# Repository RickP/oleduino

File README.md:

OLEDuino
--------

A cheap electronic name badge that can be programmed with the arduino ide. 
The ATMEGA 328 has to be preloaded with the Arduino Pro 8Mhz 3.3V bootloader.
Also chose that board when programming the badge with a 3.3V FTDI board.

All the analog ports are available for addons. 

* A source for the OLED: Search eBay for "128X64 OLED module" and pick the cheapest one with the 7 pin header on top
* A source for a battery: Any small 3.7V lithium polymer battery will do (like the ones for small RC helicopters)
* A source for the charger: http://www.ebay.com/itm/260581913847

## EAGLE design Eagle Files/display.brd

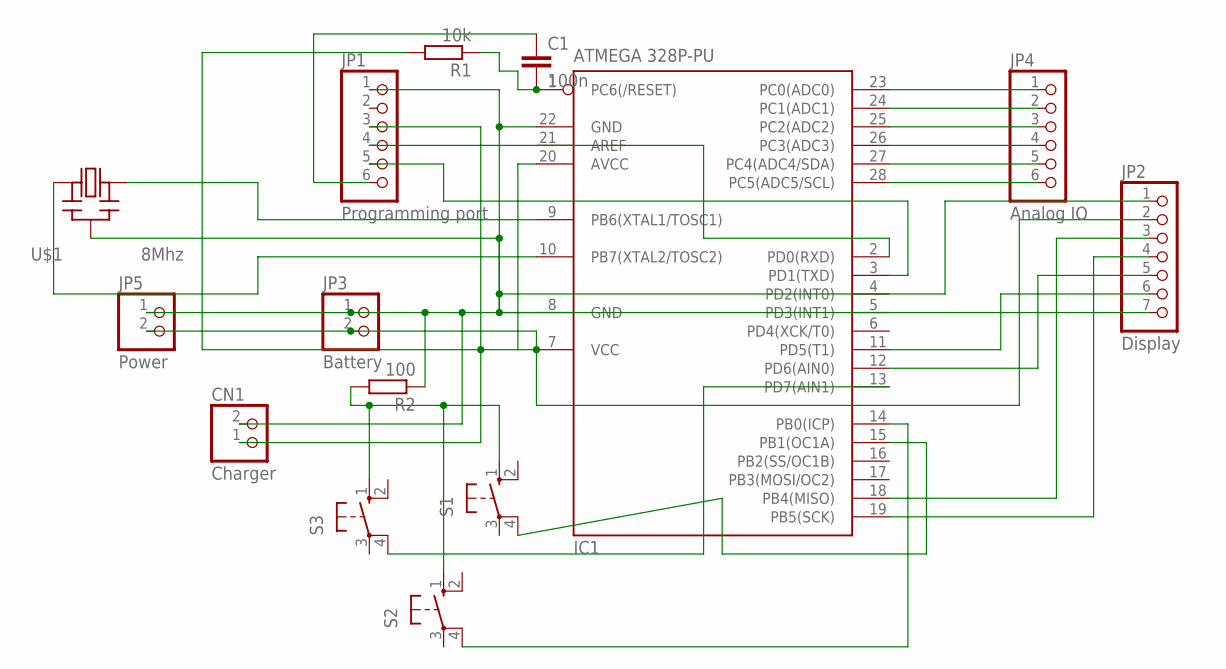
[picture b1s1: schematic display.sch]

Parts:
C1: 100n; C050-025X075
CN1: Charger; JST-PH-2-THM-RA
IC1: ATMEGA 328P-PU; DIL28-3
JP1: Programming port; 1X06/90
JP2: Display; 1X07
JP3: Battery; 1X02
JP4: Analog IO; 1X06-CLEAN
JP5: Power; 1X02
R1: 10k; 0204/7
R2: 100; 0204/7
S1, S3: 10-XX; B3F-10XX
S2: 10-XX; B3F-10XX; MPN B3F-1000
U$1: 8Mhz; CERM_OSC

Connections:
unnamed: IC1.23 (PC0(ADC0)), JP4.1
unnamed: IC1.10 (PB7(XTAL2/TOSC2)), U$1.P$1 (IN)
unnamed: IC1.19 (PB5(SCK)), JP2.4
unnamed: C1.2, IC1.1 (PC6(/RESET)), R1.1
unnamed: IC1.2 (PD0(RXD)), JP1.4
unnamed: IC1.3 (PD1(TXD)), JP1.5
unnamed: IC1.18 (PB4(MISO)), JP2.3
unnamed: CN1.1 (2), IC1.7 (VCC), IC1.20 (AVCC), JP1.3, JP2.2, JP3.2, JP5.2, R1.2
unnamed: IC1.15 (PB1(OC1A)), S1.4 (P1)
unnamed: IC1.13 (PD7(AIN1)), S3.4 (P1)
unnamed: C1.1, JP1.6
unnamed: R2.2, S1.1 (S), S2.1 (S), S3.1 (S)
unnamed: IC1.12 (PD6(AIN0)), JP2.5
unnamed: IC1.9 (PB6(XTAL1/TOSC1)), U$1.P$3 (OUT)
unnamed: IC1.11 (PD5(T1)), JP2.6
unnamed: IC1.14 (PB0(ICP)), S2.4 (P1)
unnamed: IC1.28 (PC5(ADC5/SCL)), JP4.6
unnamed: IC1.27 (PC4(ADC4/SDA)), JP4.5
unnamed: IC1.26 (PC3(ADC3)), JP4.4
unnamed: IC1.25 (PC2(ADC2)), JP4.3
unnamed: IC1.24 (PC1(ADC1)), JP4.2
unnamed: CN1.2 (1), IC1.8 (GND), IC1.22 (GND), JP1.1, JP2.1, JP2.7, JP3.1, JP5.1, R2.1, U$1.P$2 (GND)

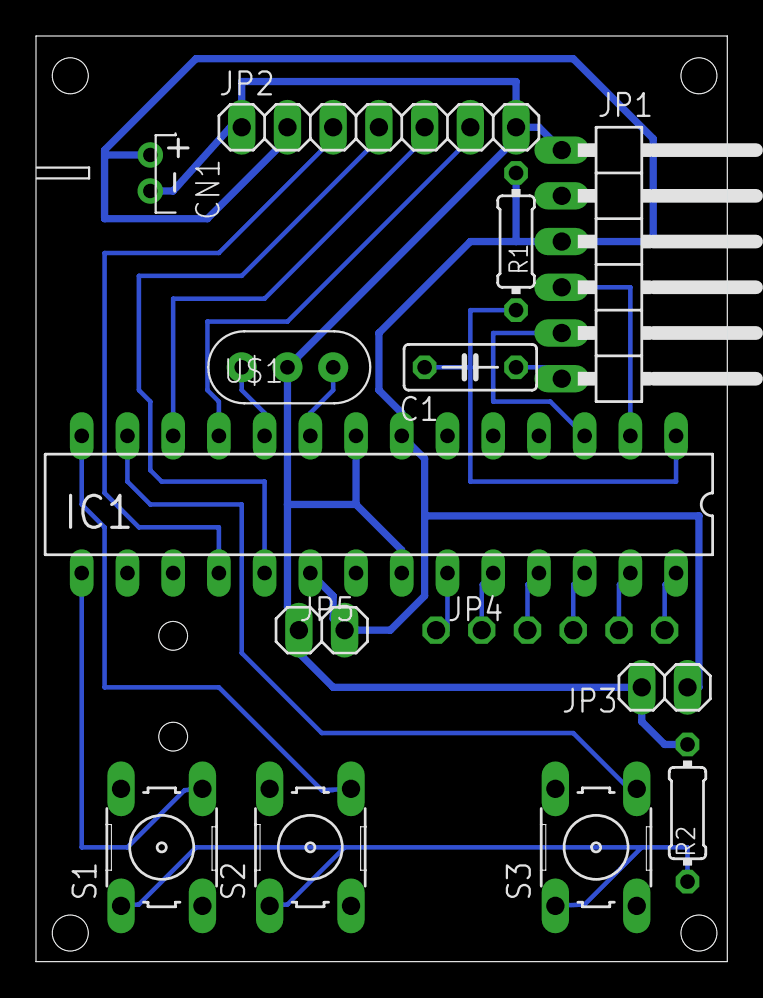
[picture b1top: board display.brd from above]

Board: 2 copper layers, 38.4 x 51.4 mm, 14 parts (0 on the bottom side), 22 nets.

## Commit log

2012-12-10 deleted stuff
2012-12-10 updated demo
2012-12-10 removed one button
2012-12-10 changed labes and positioning
2012-12-10 changed labels and positioning
2012-12-10 fixed a typo
